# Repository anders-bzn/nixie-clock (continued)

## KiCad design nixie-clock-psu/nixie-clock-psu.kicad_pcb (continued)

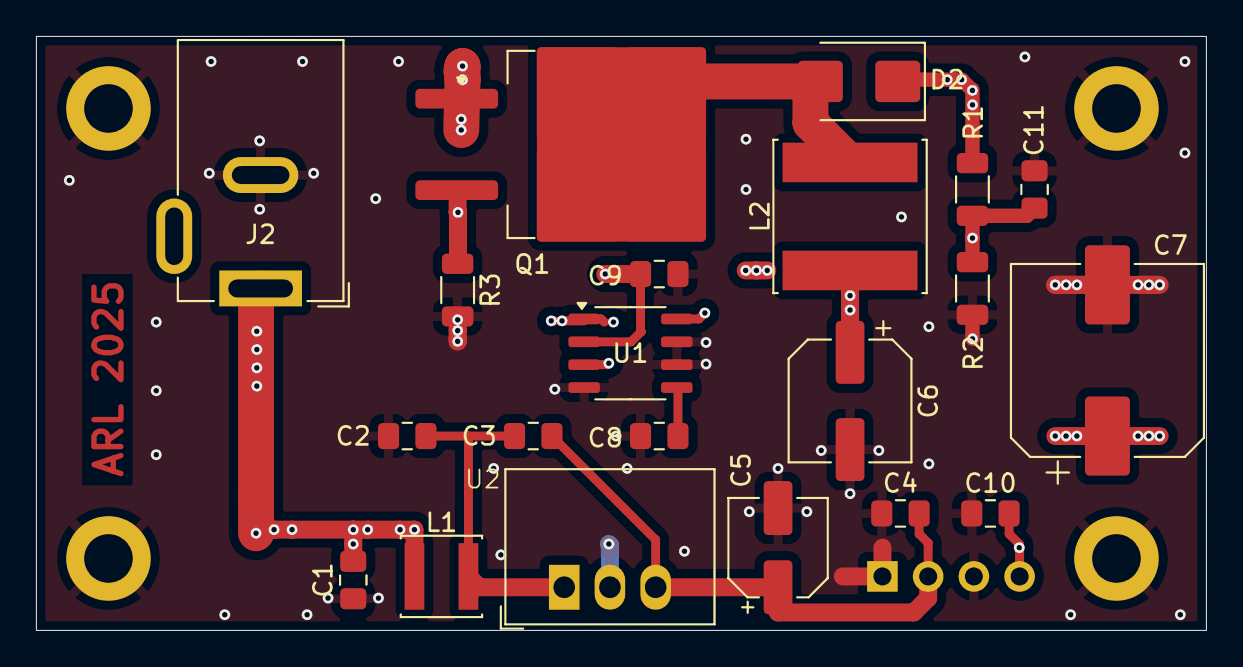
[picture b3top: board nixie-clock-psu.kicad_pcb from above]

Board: 4 copper layers, 65.0 x 33.0 mm, 26 parts (1 on the bottom side), 10 nets.

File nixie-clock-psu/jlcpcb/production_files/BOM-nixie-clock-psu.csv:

Comment,Designator,Footprint,LCSC,Quantity
R-78B5.0-0.5,U2,78xx-05A,,1
MAX1771xSA,U1,SO-8_3.9x4.9mm_P1.27mm,,1
0R10,R3,R_1206_3216Metric,,1
13k3,R2,R_1206_3216Metric,,1
1M5,R1,R_1206_3216Metric,,1
IRF644,Q1,TO-263-2,,1
100u,L2,L_Sunlord_SWPA8040S,,1
4u7,L1,L_Changjiang_FNR4030S,,1
ES2F,D2,D_SMB,,1
1n,C11,C_0805_2012Metric_Pad1.18x1.45mm_HandSolder,,1
100n,C10,C_0805_2012Metric_Pad1.18x1.45mm_HandSolder,,1
100n,C9,C_0805_2012Metric_Pad1.18x1.45mm_HandSolder,,1
100n,C8,C_0805_2012Metric_Pad1.18x1.45mm_HandSolder,,1
10uF/250V,C7,CP_Elec_10x12.5,,1
330uF/16V,C6,CP_Elec_6.3x7.7,,1
100uF/10V,C5,CP_Elec_5x5.3,,1
12V DC,J2,BarrelJack_GCT_DCJ200-10-A_Horizontal,,1
10u,C4,C_0805_2012Metric_Pad1.18x1.45mm_HandSolder,,1
1n,C3,C_0805_2012Metric_Pad1.18x1.45mm_HandSolder,,1
10u,C2,C_0805_2012Metric_Pad1.18x1.45mm_HandSolder,,1
10u,C1,C_0805_2012Metric_Pad1.18x1.45mm_HandSolder,,1
Conn_01x04_Pin,J1,PinSocket_1x04_P2.54mm_Vertical,,1

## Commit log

2025-03-15 Added sw folder
2025-03-15 Added Kicad files
2025-03-15 Add .gitignore
2025-06-23 nixie-clock-tubes: Fix small layout issue
2025-06-23 nixie-bottom: Add files
    Add files for bottom lid PCB.
2025-06-23 nixie-top: Add files
    Added files for top lid PCB.
2025-06-24 Add README.md
2025-06-24 README.md: Update
2025-06-24 README.md: Spelling
